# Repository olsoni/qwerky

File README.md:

# qwerky
A Quirky Custom Keyboard

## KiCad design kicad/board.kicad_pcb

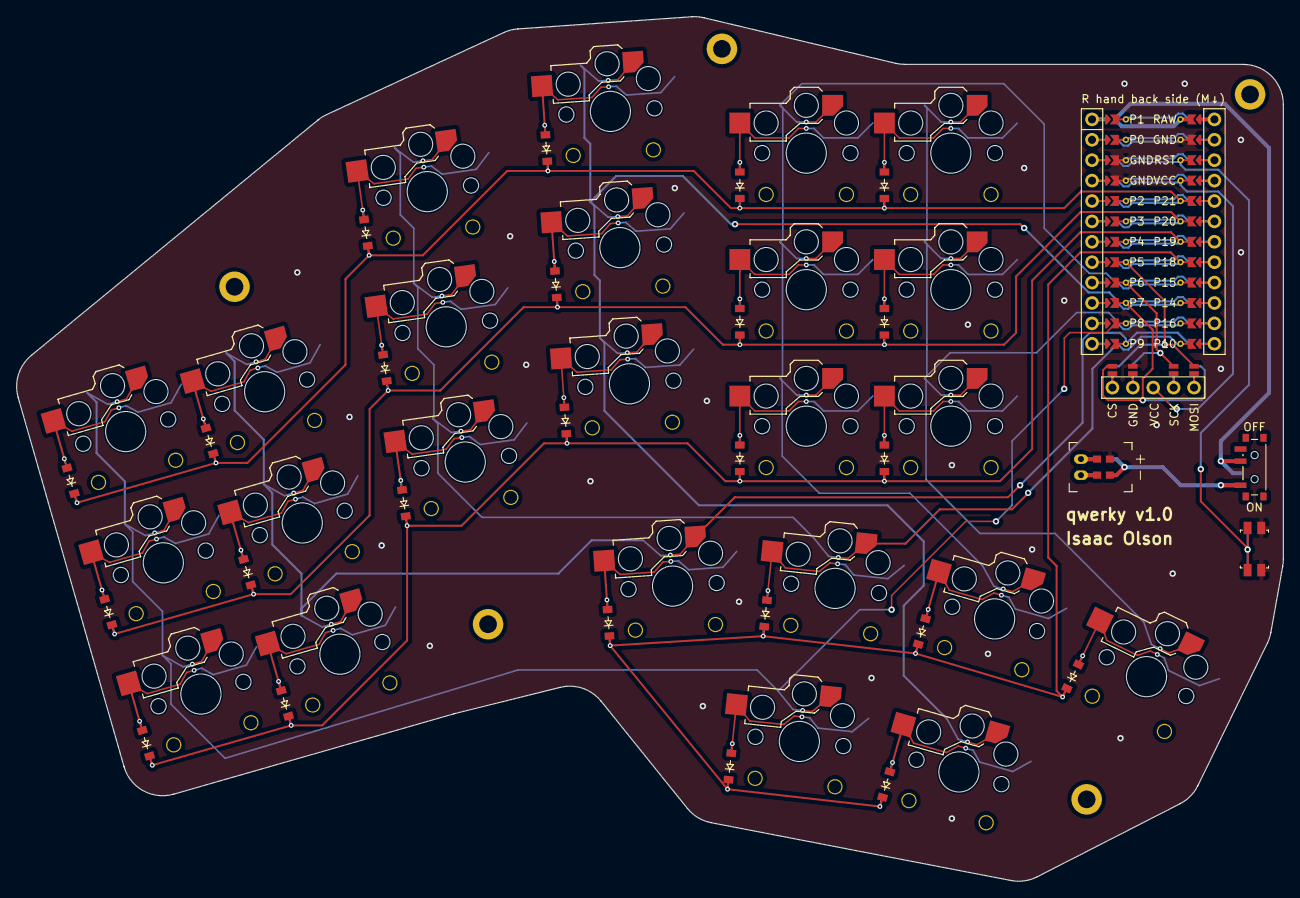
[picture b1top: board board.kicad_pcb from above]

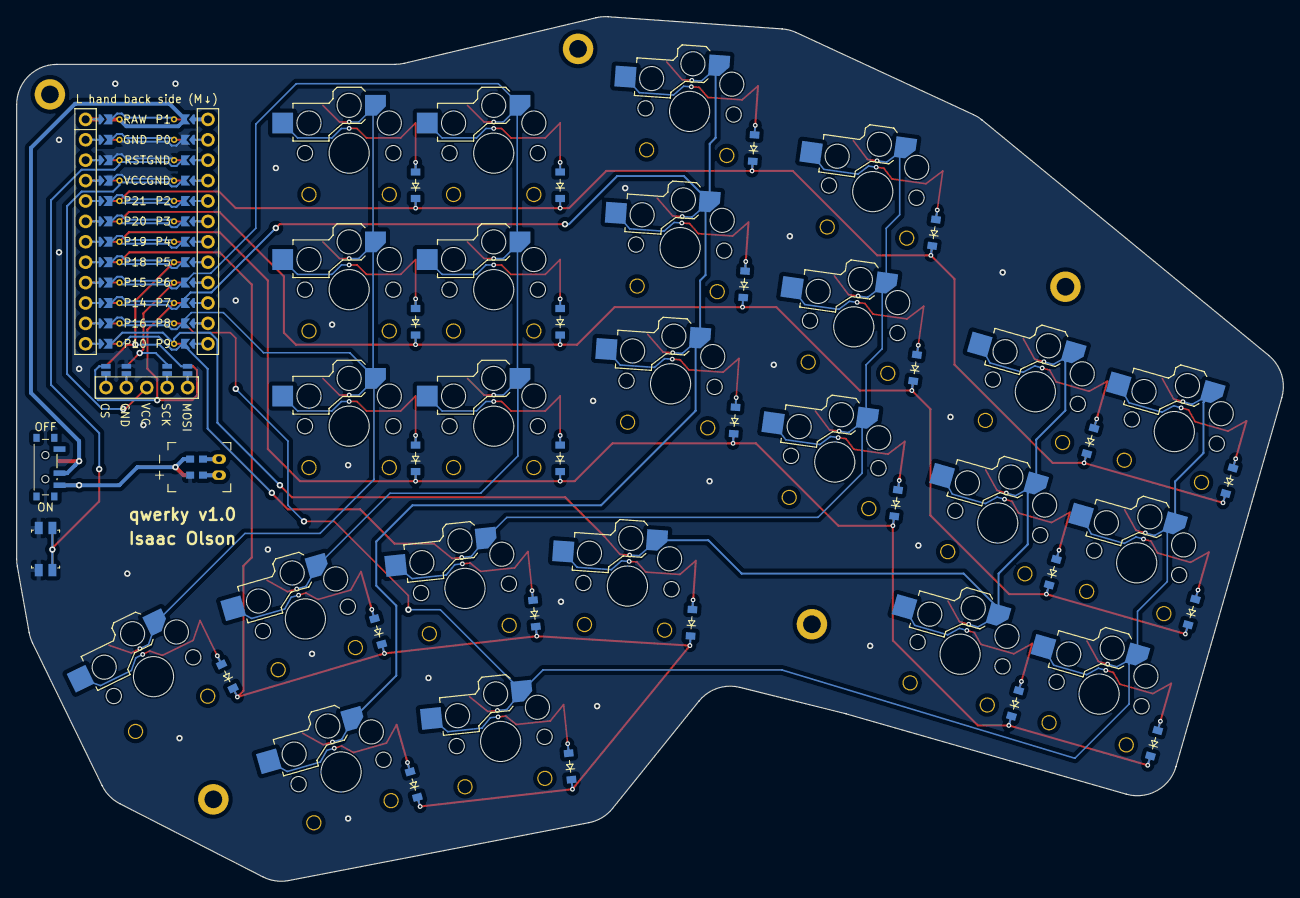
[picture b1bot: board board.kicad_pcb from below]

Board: 2 copper layers, 157.7 x 107.7 mm, 58 parts (24 on the bottom side), 48 nets.

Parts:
D1, D2, D3, D4, D5, D6, D7, D8, D9, D10, D11, D12, D13, D14, D15, D16, D17, D18, D19, D20, D21, D22, D23, D24: diode_tht_sod123
DISP1: display_nice_view
H1, H2, H3, H4, H5: mounting_hole_plated
JST1: battery_connector_jst_ph_2
MCU1: mcu_nice_nano
PWR1: power_switch_smd_side
RST1: reset_switch_smd_side
S1, S2, S3, S4, S5, S6, S7, S8, S9, S10, S11, S12, S13, S14, S15, S16, S17, S18, S19, S20, S21, S22, S23, S24: switch_choc_v1_v2

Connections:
BAT_P: JST1.1, PWR1.1, PWR1.3
CS: DISP1.14, DISP1.24, MCU1.115
DISP1_1: DISP1.1, DISP1.10, DISP1.23
DISP1_2: DISP1.2, DISP1.11, DISP1.22
DISP1_4: DISP1.4, DISP1.12, DISP1.21
DISP1_5: DISP1.5, DISP1.13, DISP1.20
GND: DISP1.15, DISP1.25, JST1.2, MCU1.102, MCU1.121, MCU1.122, RST1.1, RST1.3
JST1_1: JST1.11, JST1.21, JST1.31
JST1_2: JST1.12, JST1.22, JST1.32
MOSI: DISP1.17, DISP1.27, MCU1.117
P8: MCU1.114, S1.1, S2.1, S3.1, S23.1
P9: MCU1.113, S4.1, S5.1, S6.1, S19.1
P10: MCU1.112, S7.1, S8.1, S9.1, S20.1
P14: MCU1.110, S10.1, S11.1, S12.1, S24.1
P15: MCU1.109, S13.1, S14.1, S15.1, S21.1
P16: MCU1.111, S16.1, S17.1, S18.1, S22.1
P18: D19.1, D20.1, D21.1, D22.1, D23.1, D24.1, MCU1.108
P19: D1.1, D4.1, D7.1, D10.1, D13.1, D16.1, MCU1.107
P20: D2.1, D5.1, D8.1, D11.1, D14.1, D17.1, MCU1.106
P21: D3.1, D6.1, D9.1, D12.1, D15.1, D18.1, MCU1.105
RAW: MCU1.101, PWR1.2
RST: MCU1.103, RST1.2, RST1.4
SCK: DISP1.16, DISP1.26, MCU1.116
VCC: DISP1.3, MCU1.104
index_bottom: D13.2, S13.2
index_home: D14.2, S14.2
index_top: D15.2, S15.2
inner_bottom: D16.2, S16.2
inner_home: D17.2, S17.2
inner_top: D18.2, S18.2
middle_bottom: D10.2, S10.2
middle_home: D11.2, S11.2
middle_top: D12.2, S12.2
outer_bottom: D1.2, S1.2
outer_home: D2.2, S2.2
outer_top: D3.2, S3.2
pinky_bottom: D4.2, S4.2
pinky_home: D5.2, S5.2
pinky_top: D6.2, S6.2
ring_bottom: D7.2, S7.2
ring_home: D8.2, S8.2
ring_top: D9.2, S9.2
tb_inner_tb_bot: D24.2, S24.2
tb_outer_tb_bot: D23.2, S23.2
tt_home_tt_top: D21.2, S21.2
tt_inner_tt_top: D22.2, S22.2
tt_middle_tt_top: D20.2, S20.2
tt_outer_tt_top: D19.2, S19.2

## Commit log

2026-01-25 first config
2026-01-25 outline
2026-01-25 working our way up
2026-01-25 more footprints
2026-01-28 pretty sure the micro controller B.silk layer is wrong
2026-02-14 let's try this
2026-02-14 kicad file for reversed labels
2026-02-14 pin net syntax
2026-02-14 picked pins for the matrix
2026-02-16 adding switches and battery connector
2026-02-16 mounting holes
2026-02-16 connected display pins
2026-02-16 using better footprint for key switches
2026-02-16 hmmm, have to debug this footprint
2026-02-16 codex thinks it fixed it
2026-02-16 ok looking good
2026-02-16 well codex didn't actually quite fix the arcs right so I made them lines
2026-02-19 realizing I'm going to want to change some of the layout
2026-02-19 ready to route
2026-02-19 rebased and pulled in new footprints
2026-02-19 routing coming along nicely
2026-02-19 just need to zone fill
2026-02-20 added a ground plane
2026-02-20 random other kicad files ...
2026-02-20 making layout changes for easier routing
2026-02-20 resetting
2026-02-20 coming along quite well
2026-02-21 maybe done?
2026-02-23 things to consider:
    - add inline fuse for battery
    - lots of vias in the ground planes
    - don't bother doing ground traces
    - get the design rules off JLPCP and then put them in kicad
    - make the main power trace a bit wider (3 mm)
2026-02-24 configuring for local ergogen run
2026-02-24 improving routing
2026-02-24 minor
2026-02-27 ergogen script
2026-02-27 pretty sweet
2026-02-27 moved the keys around as desired
2026-02-27 moved components
2026-02-27 slightly larger vias for batt conn
2026-02-28 starting routing
2026-02-28 looking pretty good so far
2026-02-28 on to DRC
2026-02-28 done?
2026-02-28 removing old version
2026-02-28 fixing trace width for raw on nicenano footprint
2026-03-12 generated gerbers
2026-03-12 ignore zip
2026-05-02 starting on bom
2026-05-02 links
2026-05-02 header hunting
2026-05-02 ordered
2026-05-16 getting an assembly guide
